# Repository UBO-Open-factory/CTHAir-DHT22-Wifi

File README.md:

# CTHAir-DHT22-Wifi
Capteur de température et d'hygrométrie (DHT22) connecté à un réseau Wifi

Le capteur présenté ici permet de mesurer la température et l'hygrométrie d'un lieu puis d'envoyer ces informations par Wifi à un serveur de données.

<h1>Description</h1>
    Il intègre :
    <ul>
        <li>un capteur spécifique pouvant mesurer à la fois la température et l'hygrométrie de l'air</li>
        <li>un microcontrôleur gérant le fonctionnement de l'ensemble</li>
        <li>un chargeur de batterie  (https://www.robotshop.com/eu/fr/chargeur-batteries-lipo-micro-usb-adafruit.html?gclid=Cj0KCQiAnaeNBhCUARIsABEee8XIQpiwdCSFdvlMACDXwCc1oCrDVzvkIQyEiWymK_8KR6TJM6AMqEUaAtSwEALw_wcB)</li>
        <li>un interrupteur On/Off</li>
        <li>Quelques composants discrets pour le fonctionnement du microcontôleur.</li>
    </ul>
    Il se présente sous la forme d'un petit boitier de 58 x 50 x 26 mm perc de quelques trous intégrant la carte électronique et une batterie.

<h1>Fonctionnement</h1>
    Le module réalise une mesure de température, une mesure d'hygrométrie et une mesure de la tension de la batterie.<br>
    Il se connecte ensuite à un réseau Wifi dont on lui a comuniqué les paramètres (SSID et mot de passe).<br>
    Puis il envoie les données sur un centre de données  dont on lui a communiqué l'adresse. Parmi les données envoyées figure un identifiant qui permettra au centre de données de savoir de quel module il reçoit des informations et donc comment les enregistrer.<br>
    Enfin il se met en veille pour une durée programmée après laquelle il recommencera un cycle de mesure/envoi/sommeil...

<h1>Electronique</h1>
    <h2>Version 2.4</h2>
    Elle est composée :
    <ul>
        <li>d'une carte électronique qui mesure 36 x 44 mm. Elle est composée d'un circuit simple face. Le schéma électrique et le schéma d'implantation sont données dans le répertoire "Electronique" au format Eagle et PDF.</li>
        <li>d'un ESP8266-12 Wifi (https://www.conrad.fr/p/joy-it-esp8266-module-uart-wifi-esp12-f-1-pcs-1707668?gclid=Cj0KCQiAnaeNBhCUARIsABEee8VpehfSateDr-OI0zyCJifhymOjrz4KTu_t2pbg9GdaGwhpkJJzVcgaAu0AEALw_wcB&gclsrc=aw.ds&utm_campaign=shopping-feed&utm_content=free-google-shopping-clicks&utm_medium=surfaces&utm_source=google&utm_term=1707668&vat=true). Il est programmé pour réaliser toutes les fonctions du module. </li>
        <li>d'un chargeur pour batteries LiPo (https://www.adafruit.com/product/1904). Ce chrageur peut accepter toue batterie LiPo de 3.7V jusqu'à 5000 mAh. Il possède un prise batterie spécifique (JST2) ainsi qu'un prise de charge type USB mico.</li>
        <li>d'un capteur de température et hygrométrie relative (HR) DHT22 (https://www.robot-maker.com/shop/capteurs/31-dht22-31.html). Il peut mesurer des températures comprises entre 140 et +80°C avec une marge d'erreur de 0.5°C. Il peut mesurer un taux d'humidité de 0% à 100% avec une marge d'erreur de 2%.</li>
        <li>un régulateur "low drop" (placé côté pistes de la carte électronique) dont le rôle est de ramener la tension batterie à une tension de acceptable pour le fonctionnement du module (typiquement 3,3 V).</li>
        <li>Quelques composants dont les rôles sont multiples (filtrage d'alimentation, polarisation de certaines broches de l'ESP8266 pour le démarrage).</li>
    </ul>
    L'assemblage de la carte électronique est décrit dans le document "Assemblage" dans le répertoire "Documentation".
    <br>
    <h2>Version 3.1</h2>
    Elle est  composée des mêmes composants que l'électronique V2.4. La seule différence tient dans la carte électronique dont le schéma électrique est légèrement différent pour alimenter le DHT22 par un GPIO de l'ESP.
    Son montage est identique à la carte V2.4 à l'exception de l'emplacement des résistances. Les fichiers Eagle fournis donnent la nouvelle implantation.

<h1>Programme</h1>
    Le programme est décomposé en plusieurs fichiers disponibles dans le répertoire "programmation".
    L'ESP se programme (par exemple) avec l'IDE Arduino et à l'aide du programmateur décrit ci-dessous.
    <h2>Version 1.0</h2>
    Cette version utilise le protocole HTTP associé à un Fingerprint.
    <ul>
        <li>Le fichier "CTHAir_DHT22_Wifi_v1_0.ino" qui contient le programme principal.</li>
        <li>Le fichier "variables.h" qui contient les variables principales de fonctionnement du programme. Notamment l'identifiant du module qui sera transmis avec les données mesurées. Cet identifiant permettra qu centre de données de savoir quel module envoie des données.</li>
        <li>Le fichier "wifi_data.h" qui contient les paramètres de connection à un réseau Wifi. Les deux paramètres sont a adapter en fonction du réseau auquel on veut se connecter.</li>
        <li>Le fichier "server_data.h" qui contient les paramètres du serveur de données sur lequel on veut envoyer les données (hote, URL, port et fingerprint).</li>
        <li>Le fichier "type_converter.h" qui contient quelques fonctions utiles pour trnasformer des variables numériques en chaines de caractères formatées.</li>
    </ul>
    il est nécessaire de renseigner : 
        ssid et mod de passe dans le fichier "wifi_data.h"
        host, url et fingerprint dans le fichier "server_data.h"
        identifiant dans "variables.h"
    <br>
<h2>Version 1.1</h2>
    Dérivée de la version 1.0 elle n'utilise plus de fingerprint. LE reste fonctionne de la même manière.
    Il sera donc nécessaire de renseigner les mêmes données que dans la version 1.0 (sauf le fingerprint) avant de programmer l'ESP12.
    <h2>Version 2.0</h2>
    Similaire à la version 1.0 sur le plan de l'organisation. Seul la partie principale change pour s'adapter à l'alimentation du DHT22 par un GPIO.
    De ce fait il sera nécessaire de renseigner les mêmes données que dans la version 1.0 (sauf le fingerprint) avant de programmer l'ESP12.

<h1>Programmateur V1</h1>
    La programmation de l'ESP nécessite passe par une liaison UART et un convertisseur UART/USB pour communiquer avec un ordinateur de bureau. La solution adoptée a été de modifier un NodeMCU en enlevant l'ESP présent sur celui-ci et en le remplaçant par deux connecteurs. Ceci permet d'insérer des ESP à programmer.<br>
    Mise en garde : le désoudage de l'ESP et la soudure des connecteurs est un peu délicate. Une photo du programmateur est dsponible dans le répertoire "programmateur"

<h1>Batteries</h1>
    Les batteries utilisables sont de type LiPo 3.7V. Plusieurs capacités sont disponibles (250 mAh, 400 mAh, 1000 mAh et 5000 mAh).

<h1>Boitier V1</h1>
        Cette version n'accepte que les batteries jusqu'à 1000mAh inclus.
        LEs plans sont donnés dans le répertoire "Boitier V1"

<h1>Table de compatibilité</h1>
    Le tableau suivant indique les compatibilités entre le matériel et le logiciel.
<table>
    <tr>
        <td></td>
        <td><b>UOFPROTO2</b></td>
        <td><b>UOFPROTO3</b></td>
    </tr>
    <tr>
        <td><b>Electronique</b></td>
        <td>V 2.4</td>
        <td>V 3.1</td>
    </tr>
    <tr>
        <td><b>Programme</b></td>
        <td>V1.0<br>V1.1</td>
        <td>V2.0</td>
    </tr>
    <tr>
        <td><b>Boitier</b></td>
        <td>V1</td>
        <td>V1</td>
    </tr>
    <tr>
        <td><b>Programmateur</b></td>
        <td>V1</td>
        <td>V1</td>
    </tr>
</table>

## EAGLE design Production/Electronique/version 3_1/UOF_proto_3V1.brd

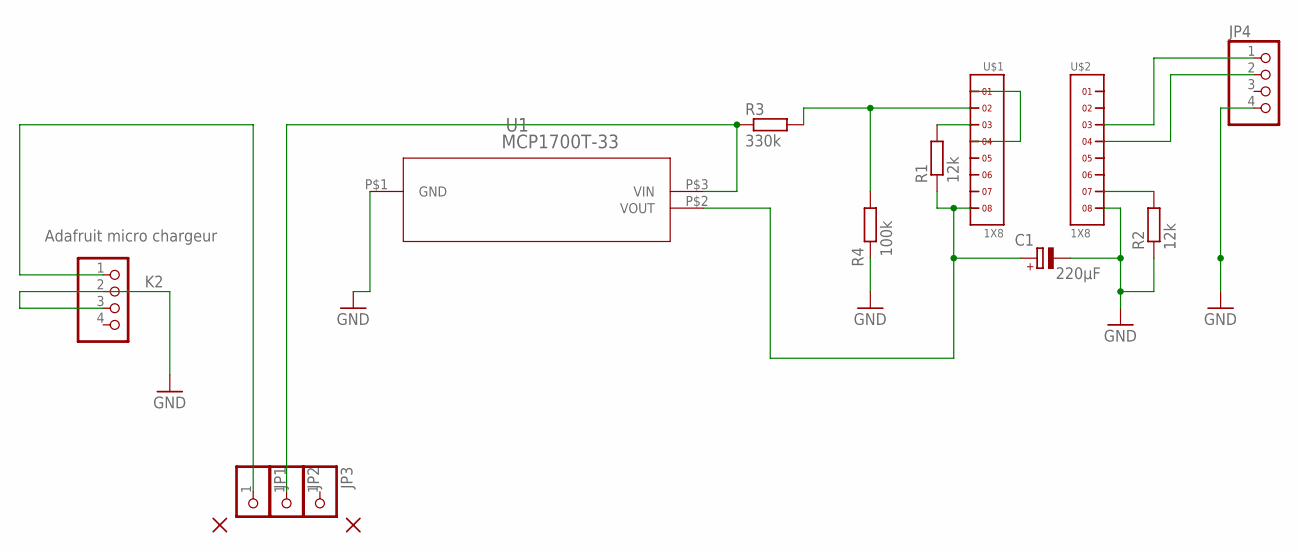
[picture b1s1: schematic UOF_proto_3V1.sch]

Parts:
C1: 220µF; E5-10,5
JP1, JP2, JP3: PINHD-1X1; 1X01
JP4: PINHD-1X4; 1X04
K2: Adafruit micro chargeur; 1X04
PAD4, PAD5: N_2,0/1,5; 2,0/1,5
R1, R2: 12k; 0207/10
R3: 330k; 0207/10
R4: 100k; 0207/10
U1: MCP1700T-33; SOT-23
U$1, U$2: 1X8

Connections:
GND: C1.-, JP4.4, K2.2, K2.3, R2.1, R4.2, U1.P$1 (GND), U$2.8
unnamed: JP4.2, U$2.4
unnamed: R3.2, R4.1, U$1.2
unnamed: JP1.1, K2.1
unnamed: R2.2, U$2.7
unnamed: C1.+, R1.1, U1.P$2 (VOUT), U$1.8
unnamed: U$1.1, U$1.4
unnamed: JP2.1, R3.1, U1.P$3 (VIN)
unnamed: R1.2, U$1.3
unnamed: JP4.1, U$2.3

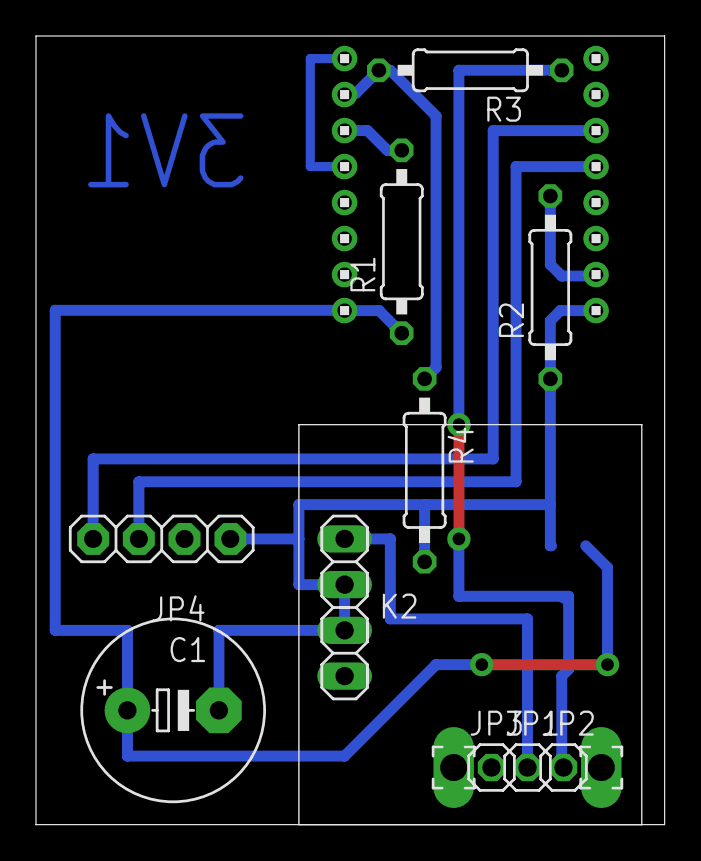
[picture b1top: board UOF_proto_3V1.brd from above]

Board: 2 copper layers, 34.9 x 43.8 mm, 15 parts (1 on the bottom side), 10 nets.

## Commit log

2021-11-25 essai
2021-12-06 Création
2021-12-06 Mise en forme readme
2022-01-18 implémentation de versions
    Ajout des version 1.1 et 2 pour le logiciel, 3.1 pour l'électronique
2022-01-18 correction de mise en page du read me
2022-01-18 mise en page readme
